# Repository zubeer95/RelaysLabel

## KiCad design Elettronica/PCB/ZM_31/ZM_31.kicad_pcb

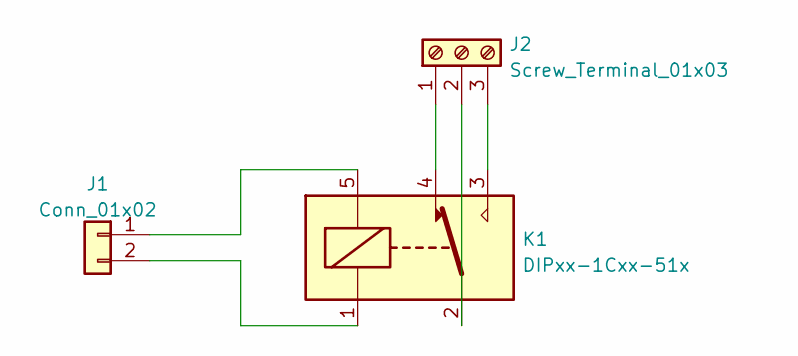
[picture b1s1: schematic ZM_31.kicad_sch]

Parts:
J1: Conn_01x02; Molex_KK-396_A-41791-0002_1x02_P3.96mm_Vertical
J2: Screw_Terminal_01x03; PhoenixContact_MCV_1,5_3-G-3.5_1x03_P3.50mm_Vertical
K1: DIPxx-1Cxx-51x; Relay_SPDT_Omron-G5Q-1

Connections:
unnamed: J1.1, K1.5
unnamed: J1.2, K1.1
unnamed: J2.1, K1.4
unnamed: J2.2, K1.2
unnamed: J2.3, K1.3

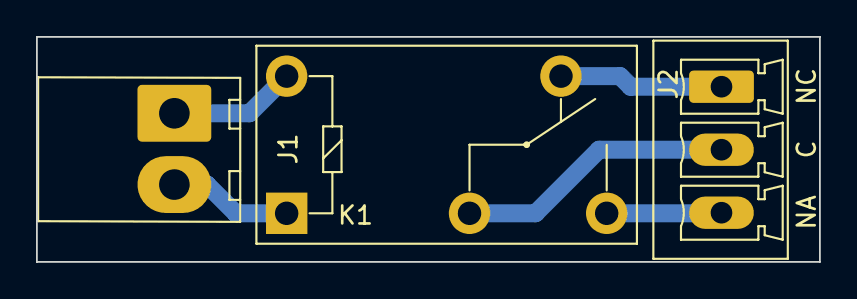
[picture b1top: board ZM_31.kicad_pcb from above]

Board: 2 copper layers, 43.5 x 12.5 mm, 3 parts (0 on the bottom side), 5 nets.
